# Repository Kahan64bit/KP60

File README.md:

# Custom 60% Keyboard PCB 

This is a custom-designed **60%** keyboard PCB created for mechanical keyboard enthusiasts who want full control over their build, layout, and firmware. The PCB is fully compatible with QMK/VIA and uses the QWERTY layout standard.

PCB dimensions have been made to fit [Tofu60 Redux Case](https://kbdfans.com/products/tofu60-redux-case?variant=42164599750795). More specification related information can be found below.

## Features

-  **QMK/VIA Compatible**
-  **USB-C Connector**
-  **Solder-Only Sockets**
-  **ESD Protection & Power Filtering**
-  **Standard 60% QWERTY Layout (ANSI support)**
-  **Overcurrent Protection**
-  **STM32 MCU**

## Specifications 

| Feature              | Details                         |
|----------------------|---------------------------------|
| Microcontroller      | STM32F072CBT6                      |
| Connector            | USB-C                           |
| Switch Compatibility | MX-style (5-pin support) |
| Firmware Support     | QMK, VIA                        |
| Matrix               | 5x14 (standard 60% matrix)      |
| Dimensions           | Standard 60% mounting holes     |
| Auxiliary            | ESD + Decoupling + Reset     |
| Misc                 | 3V3 Regulator  |

## Schematic 

## Diode Matrix 

## LED Matrix 

## PCB 

## Final Build

## Render 
Click **[Render](https://github.com/Kahan64bit/KP60/blob/main/KP60/Images/PCB_Render.gif)** to see 3D Render

##  Roadmap  (Will be added as a seperate macroboard)

The KP60 project is actively evolving to support a broader range of features for keyboard customizers and enthusiasts. Here's a sneak peek at what’s coming in future versions:

### 🛠 Planned Features

-  **OLED Screen Integration**  
  Support for a 128x32 OLED screen for displaying layers, animations, or custom text.

-  **Hot-Swap Socket Support**  
  Enable easy switch swapping without soldering.

-  **Rotary Encoder Support**  
  Optional encoder support for volume, media, and custom actions.

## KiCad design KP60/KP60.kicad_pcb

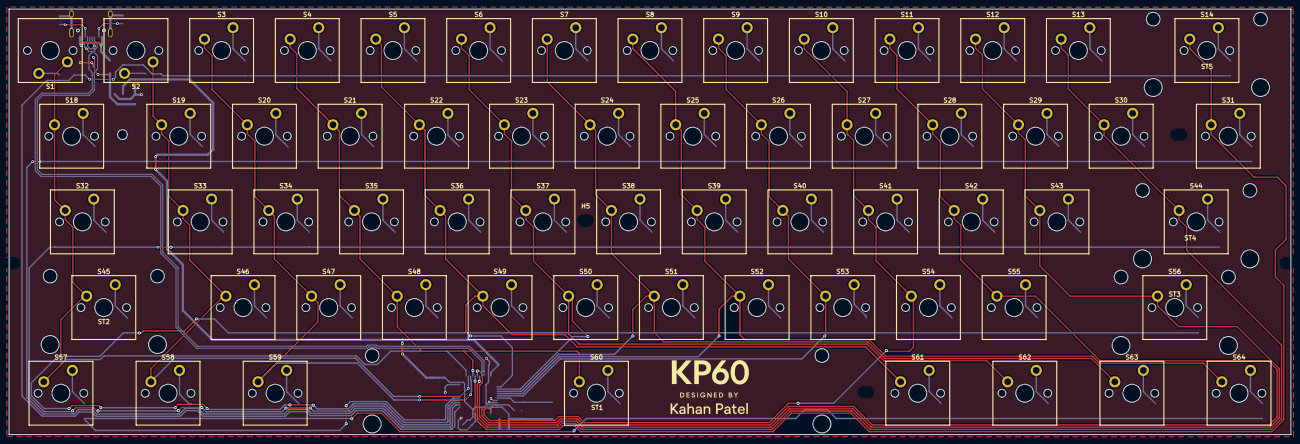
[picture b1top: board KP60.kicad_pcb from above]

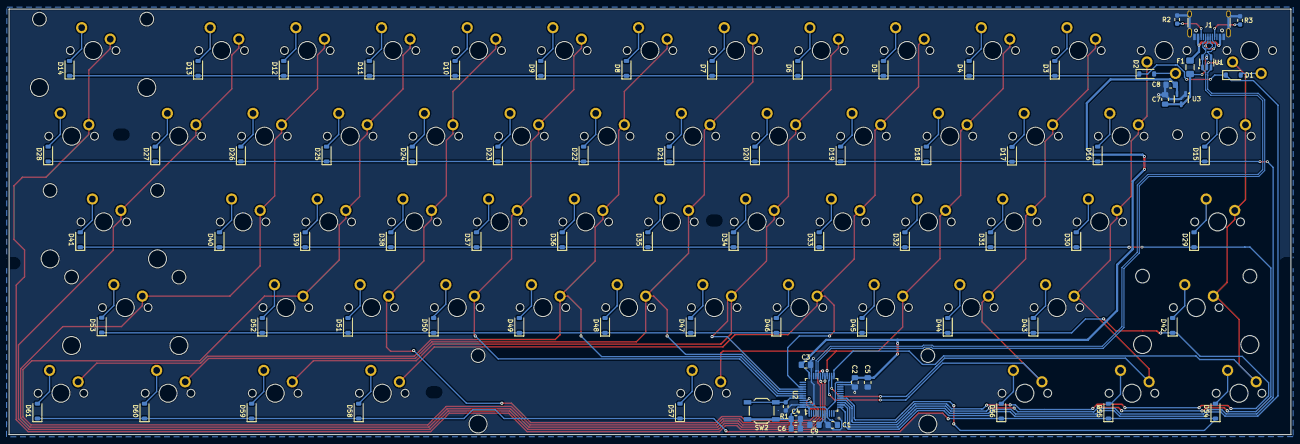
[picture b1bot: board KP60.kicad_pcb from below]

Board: 2 copper layers, 285.0 x 94.6 mm, 151 parts (79 on the bottom side), 90 nets.

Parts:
C1, C2, C3, C4, C5, C9: 100n; C_0805_2012Metric_Pad1.18x1.45mm_HandSolder
C6: 10u; C_0805_2012Metric_Pad1.18x1.45mm_HandSolder
C7, C8: 1u; C_0805_2012Metric_Pad1.18x1.45mm_HandSolder
D1, D2, D3, D4, D5, D6, D7, D8, D9, D10, D11, D12, D13, D14, D15, D16, D17, D18, D19, D20, D21, D22, D23, D24, D25, D26, D27, D28, D29, D30, D31, D32, D33, D34, D35, D36, D37, D38, D39, D40, D41, D42, D43, D44, D45, D46, D47, D48, D49, D50, D51, D52, D53, D54, D55, D56, D57, D58, D59, D60, D61: Diode; D_SOD-123
F1: 500mA; Fuse_1206_3216Metric_Pad1.42x1.75mm_HandSolder
H1, H2, H3, H4, H5, H6: MountingHole_2.2mm_M2
J1: USB_C_Receptacle_USB2.0_14P; USB_C_Receptacle_HRO_TYPE-C-31-M-12
R1: 10k; R_0603_1608Metric_Pad0.98x0.95mm_HandSolder
R2, R3: 5k1; R_0603_1608Metric_Pad0.98x0.95mm_HandSolder
S1: Esc; MX_PCB_1.00u
S2: 1; MX_PCB_1.00u
S3: 2; MX_PCB_1.00u
S4: 3; MX_PCB_1.00u
S5: 4; MX_PCB_1.00u
S6: 5; MX_PCB_1.00u
S7: 6; MX_PCB_1.00u
S8: 7; MX_PCB_1.00u
S9: 8; MX_PCB_1.00u
S10: 9; MX_PCB_1.00u
S11: 0; MX_PCB_1.00u
S12: -; MX_PCB_1.00u
S13: =; MX_PCB_1.00u
S14: backspace; MX_PCB_2.00u
S18: tab; MX_PCB_1.50u
S19: q; MX_PCB_1.00u
S20: w; MX_PCB_1.00u
S21: e; MX_PCB_1.00u
S22: r; MX_PCB_1.00u
S23: t; MX_PCB_1.00u
S24: y; MX_PCB_1.00u
S25: u; MX_PCB_1.00u
S26: i; MX_PCB_1.00u
S27: o; MX_PCB_1.00u
S28: p; MX_PCB_1.00u
S29: {; MX_PCB_1.00u
S30: }; MX_PCB_1.00u
S31: \; MX_PCB_1.50u
S32: caps; MX_PCB_1.75u
S33: a; MX_PCB_1.00u
S34: s; MX_PCB_1.00u
S35: d; MX_PCB_1.00u
S36: f; MX_PCB_1.00u
S37: g; MX_PCB_1.00u
S38: h; MX_PCB_1.00u
S39: j; MX_PCB_1.00u
S40: k; MX_PCB_1.00u
S41: l; MX_PCB_1.00u
S42: ;; MX_PCB_1.00u
S43: "; MX_PCB_1.00u
S44: enter; MX_PCB_2.25u
S45: Lshift; MX_PCB_2.25u
S46: z; MX_PCB_1.00u
S47: x; MX_PCB_1.00u
S48: c; MX_PCB_1.00u
S49: v; MX_PCB_1.00u
S50: b; MX_PCB_1.00u
S51: n; MX_PCB_1.00u
S52: m; MX_PCB_1.00u
S53: ,; MX_PCB_1.00u
S54: .; MX_PCB_1.00u
S55: /; MX_PCB_1.00u
S56: Rshift; MX_PCB_2.75u
S57: Lctrl; MX_PCB_1.25u
S58: Lsuper; MX_PCB_1.25u
S59: Lalt; MX_PCB_1.25u
S60: space; MX_PCB_6.25u
S61: Ralt; MX_PCB_1.25u
S62: Rsuper; MX_PCB_1.25u
S63: Fn; MX_PCB_1.25u
S64: Rctrl; MX_PCB_1.25u
ST1: Stabilizer_MX_6.25u
ST2, ST3, ST4, ST5: Stabilizer_MX_2.00u
SW2: SW_Push; SW_SPST_TL3342
U1: USBLC6-2SC6; SOT-23-6
U2: STM32F072CBTx; LQFP-48_7x7mm_P0.5mm
U3: XC6206PxxxMR; SOT-23-3

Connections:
+3.3V: C1.1, C2.1, C3.1, C4.1, C5.1, C6.1, C8.1, SW2.1, U2.1 (VBAT), U2.9 (VDDA), U2.24 (VDD), U2.36 (VDDIO2), U2.48 (VDD), U3.2 (VO)
+5V: C7.1, F1.2, U1.5 (VBUS), U3.3 (VI)
/NRST: C9.2, U2.7 (NRST)
A3: D1.1 (K), D2.1 (K), D3.1 (K), D4.1 (K), D5.1 (K), D6.1 (K), D7.1 (K), D8.1 (K), D9.1 (K), D10.1 (K), D11.1 (K), D12.1 (K), D13.1 (K), D14.1 (K), U2.13 (PA3)
A4: D15.1 (K), D16.1 (K), D17.1 (K), D18.1 (K), D19.1 (K), D20.1 (K), D21.1 (K), D22.1 (K), D23.1 (K), D24.1 (K), D25.1 (K), D26.1 (K), D27.1 (K), D28.1 (K), U2.14 (PA4)
A5: D29.1 (K), D30.1 (K), D31.1 (K), D32.1 (K), D33.1 (K), D34.1 (K), D35.1 (K), D36.1 (K), D37.1 (K), D38.1 (K), D39.1 (K), D40.1 (K), D41.1 (K), U2.15 (PA5)
A6: D42.1 (K), D43.1 (K), D44.1 (K), D45.1 (K), D46.1 (K), D47.1 (K), D48.1 (K), D49.1 (K), D50.1 (K), D51.1 (K), D52.1 (K), D53.1 (K), U2.16 (PA6)
A7: D54.1 (K), D55.1 (K), D56.1 (K), D57.1 (K), D58.1 (K), D59.1 (K), D60.1 (K), D61.1 (K), U2.17 (PA7)
A8: S14.1, S31.1, U2.29 (PA8)
B3: S5.1, S22.1, S36.1, S49.1, S61.1, U2.39 (PB3)
B4: S6.1, S23.1, S37.1, S50.1, S62.1, U2.40 (PB4)
B5: S7.1, S24.1, S38.1, S51.1, S63.1, U2.41 (PB5)
B6: S8.1, S25.1, S39.1, S52.1, S64.1, U2.42 (PB6)
B7: S9.1, S26.1, S40.1, S53.1, U2.43 (PB7)
B8: S10.1, S27.1, S41.1, S54.1, U2.45 (PB8)
B9: S11.1, S28.1, S42.1, S55.1, U2.46 (PB9)
B12: S1.1, S18.1, S32.1, S45.1, S57.1, U2.25 (PB12)
B13: S2.1, S19.1, S33.1, S46.1, S58.1, U2.26 (PB13)
B14: S3.1, S20.1, S34.1, S47.1, S59.1, U2.27 (PB14)
B15: S4.1, S21.1, S35.1, S48.1, S60.1, U2.28 (PB15)
B30: S12.1, S29.1, S43.1, S56.1, U2.30 (PA9)
B31: S13.1, S30.1, S44.1, U2.31 (PA10)
BOOT0: R1.1, SW2.2, U2.44 (BOOT0)
D+: J1.A6 (D+), J1.B6 (D+), U1.1 (I/O1), U1.6 (I/O1), U2.33 (PA12)
D-: J1.A7 (D-), J1.B7 (D-), U1.3 (I/O2), U1.4 (I/O2), U2.32 (PA11)
GND: C1.2, C2.2, C3.2, C4.2, C5.2, C6.2, C7.2, C8.2, C9.1, J1.A1 (GND), J1.A12 (GND), J1.B1 (GND), J1.B12 (GND), J1.S1 (SHIELD), R1.2, R2.1, R3.1, U1.2 (GND), U2.8 (VSSA), U2.23 (VSS), U2.35 (VSS), U2.47 (VSS), U3.1 (GND)
unnamed: D1.2 (A), S1.2
unnamed: D2.2 (A), S2.2
unnamed: D3.2 (A), S3.2
unnamed: D4.2 (A), S4.2
unnamed: D5.2 (A), S5.2
unnamed: D6.2 (A), S6.2
unnamed: D7.2 (A), S7.2
unnamed: D8.2 (A), S8.2
unnamed: D9.2 (A), S9.2
unnamed: D10.2 (A), S10.2
unnamed: D11.2 (A), S11.2
unnamed: D12.2 (A), S12.2
unnamed: D13.2 (A), S13.2
unnamed: D14.2 (A), S14.2
unnamed: D15.2 (A), S18.2
unnamed: D16.2 (A), S19.2
unnamed: D17.2 (A), S20.2
unnamed: D18.2 (A), S21.2
unnamed: D19.2 (A), S22.2
unnamed: D20.2 (A), S23.2
unnamed: D21.2 (A), S24.2
unnamed: D22.2 (A), S25.2
unnamed: D23.2 (A), S26.2
unnamed: D24.2 (A), S27.2
unnamed: D25.2 (A), S28.2
unnamed: D26.2 (A), S29.2
unnamed: D27.2 (A), S30.2
unnamed: D28.2 (A), S31.2
unnamed: D29.2 (A), S32.2
unnamed: D30.2 (A), S33.2
unnamed: D31.2 (A), S34.2
unnamed: D32.2 (A), S35.2
unnamed: D33.2 (A), S36.2
unnamed: D34.2 (A), S37.2
unnamed: D35.2 (A), S38.2
unnamed: D36.2 (A), S39.2
unnamed: D37.2 (A), S40.2
unnamed: D38.2 (A), S41.2
unnamed: D39.2 (A), S42.2
unnamed: D40.2 (A), S43.2
unnamed: D41.2 (A), S44.2
unnamed: D42.2 (A), S45.2
unnamed: D43.2 (A), S46.2
unnamed: D44.2 (A), S47.2
unnamed: D45.2 (A), S48.2
unnamed: D46.2 (A), S49.2
unnamed: D47.2 (A), S50.2
unnamed: D48.2 (A), S51.2
unnamed: D49.2 (A), S52.2
unnamed: D50.2 (A), S53.2
unnamed: D51.2 (A), S54.2
unnamed: D52.2 (A), S55.2
unnamed: D53.2 (A), S56.2
unnamed: D54.2 (A), S57.2
unnamed: D55.2 (A), S58.2
unnamed: D56.2 (A), S59.2
unnamed: D57.2 (A), S60.2
unnamed: D58.2 (A), S61.2
unnamed: D59.2 (A), S62.2
unnamed: D60.2 (A), S63.2
unnamed: D61.2 (A), S64.2
unnamed: J1.A5 (CC1), R3.2
unnamed: J1.B5 (CC2), R2.2
VBUS: F1.1, J1.A4 (VBUS), J1.A9 (VBUS), J1.B4 (VBUS), J1.B9 (VBUS)

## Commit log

2025-03-18 Added Footprints + Symbols
2025-03-19 Completed MCU Circuit and USB Circuit
2025-03-19 Passed Electric Rules Check // Will work on cleaning up schematic then beginning PCB design
2025-03-19 Formatted Matrix
2025-03-21 Working on PCB // Laid out key switches // 60% board
2025-03-21 Cleaned up rats nest
2025-03-22 Added traces to matrix
2025-03-23 Added mounting moles + stabilizers WIP
2025-03-24 80% of signal traces are complete
2025-03-30 All traces done. Now working on grounding.
2025-03-30 Optimized Traces + Fixed Silkscreen DRC Errors
2025-04-07 Added Ground Filled Zones + Finished All Traces // Working on final touches
2025-04-07 Fixed misc DRC errors // Reviewing
2025-04-08 Adding silkscreen + polish
2025-04-08 Polishing Cont.
2025-05-02 Revisional Changes
2025-05-02 add measurements + pictures
2025-05-04 upload design images for readme
2025-05-04 more images + naming fixes
2025-05-04 add better gif
2025-05-05 polish
2025-05-11 add led matrix circuit + passed ERC
2025-05-11 generated gerbers
2025-05-19 Create LICENCE
2025-06-03 Formatting Changes
2025-09-24 Added Matrix Pic
2025-09-24 Keyboard picture update
2025-11-07 Mechanical Changes
2025-11-07 Misc
2025-11-07 diff. trace tweaks
2026-05-25 Revise layout support and roadmap in README
    Removed layout support details and updated roadmap section.
2026-05-25 Refactor README.md for improved structure and formatting
    Updated formatting and section titles in README.md for consistency and clarity.
